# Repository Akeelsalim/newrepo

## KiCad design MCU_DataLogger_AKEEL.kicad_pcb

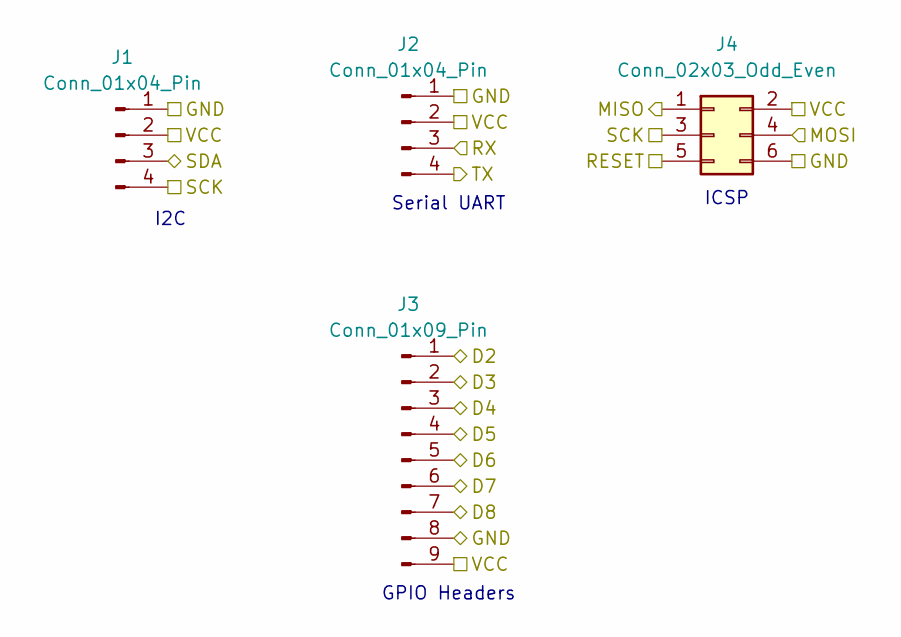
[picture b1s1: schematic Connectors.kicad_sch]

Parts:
J1, J2: Conn_01x04_Pin; PinHeader_1x04_P2.54mm_Vertical
J3: Conn_01x09_Pin; PinHeader_1x09_P2.54mm_Vertical
J4: Conn_02x03_Odd_Even; PinHeader_2x03_P2.54mm_Vertical

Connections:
/D2: J3.1; also elsewhere on the board
/D3: J3.2; also elsewhere on the board
/D4: J3.3; also elsewhere on the board
/D5: J3.4; also elsewhere on the board
/D6: J3.5; also elsewhere on the board
/D7: J3.6; also elsewhere on the board
/D8: J3.7; also elsewhere on the board
/MISO: J4.1; also elsewhere on the board
/MOSI: J4.4; also elsewhere on the board
/RESET: J4.5; also elsewhere on the board
/RX: J2.3; also elsewhere on the board
/SCK: J1.4, J4.3; also elsewhere on the board
/SDA: J1.3; also elsewhere on the board
/TX: J2.4; also elsewhere on the board
/VCC: J1.2, J2.2, J3.9, J4.2; also elsewhere on the board
GND: J1.1, J2.1, J3.8, J4.6; also elsewhere on the board

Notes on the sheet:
ICSP
Serial UART
I2C
GPIO Headers

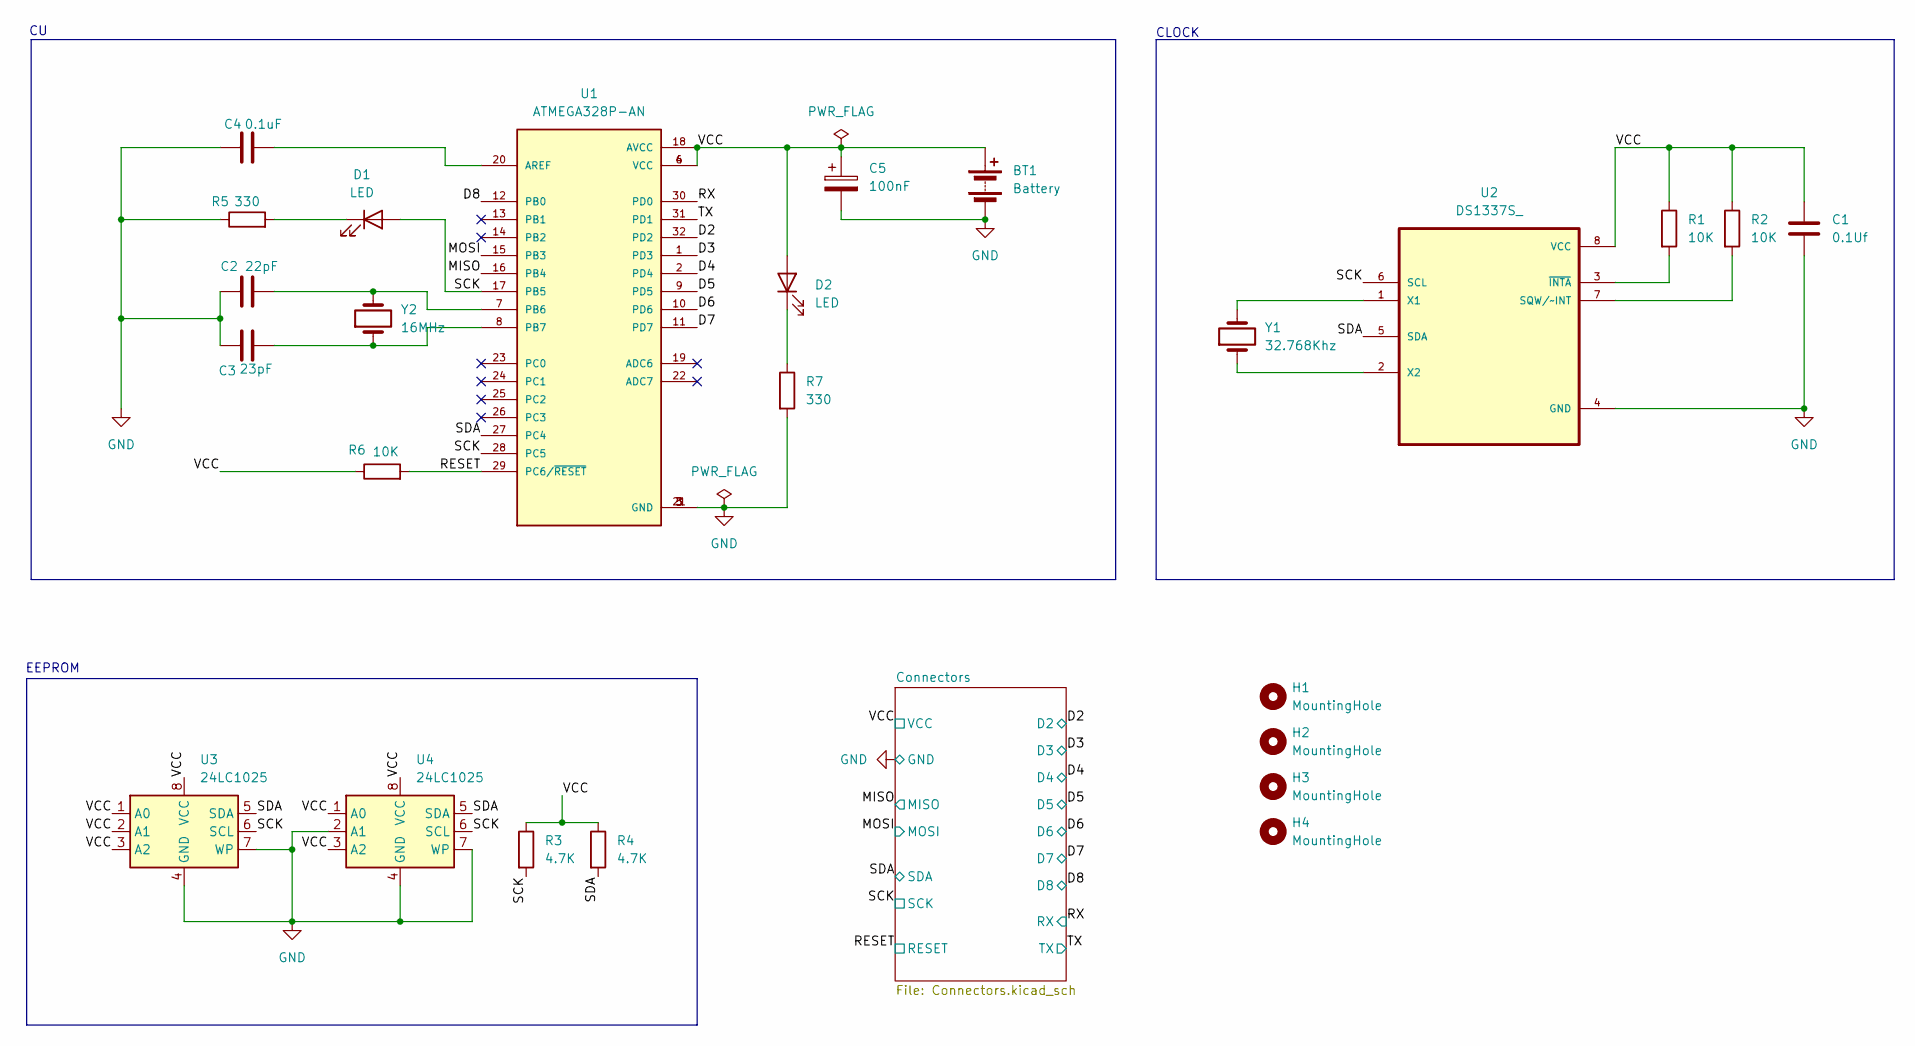
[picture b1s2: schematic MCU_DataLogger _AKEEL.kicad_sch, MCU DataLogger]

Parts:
BT1: Battery; PinHeader_1x02_P2.54mm_Vertical
C1: 0.1Uf; C_0805_2012Metric
C2: 22pF; C_0805_2012Metric
C3: 23pF; C_0805_2012Metric
C4: 0.1uF; C_0805_2012Metric
C5: 100nF; C_0805_2012Metric
D1, D2: LED; LED_0805_2012Metric
H1, H2, H3, H4: MountingHole; MountingHole_2.1mm
R1, R2, R6: 10K; R_0805_2012Metric
R3, R4: 4.7K; R_0805_2012Metric
R5, R7: 330; R_0805_2012Metric
U1: ATMEGA328P-AN; Atmega328p-AN
U2: DS1337S_; DS1337S
U3, U4: 24LC1025; SOIC-8_5.3x5.3mm_P1.27mm
Y1: 32.768Khz; Crystal_SMD_5032-2Pin_5.0x3.2mm_HandSoldering
Y2: 16MHz; Crystal_SMD_5032-2Pin_5.0x3.2mm_HandSoldering

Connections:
/D2: U1.32 (PD2); also elsewhere on the board
/D3: U1.1 (PD3); also elsewhere on the board
/D4: U1.2 (PD4); also elsewhere on the board
/D5: U1.9 (PD5); also elsewhere on the board
/D6: U1.10 (PD6); also elsewhere on the board
/D7: U1.11 (PD7); also elsewhere on the board
/D8: U1.12 (PB0); also elsewhere on the board
/MISO: U1.16 (PB4); also elsewhere on the board
/MOSI: U1.15 (PB3); also elsewhere on the board
/RESET: R6.2, U1.29 (PC6/~RESET); also elsewhere on the board
/RX: U1.30 (PD0); also elsewhere on the board
/SCK: D1.2 (A), R3.2, U1.17 (PB5), U1.28 (PC5), U2.6 (SCL), U3.6 (SCL), U4.6 (SCL); also elsewhere on the board
/SDA: R4.2, U1.27 (PC4), U2.5 (SDA), U3.5 (SDA), U4.5 (SDA); also elsewhere on the board
/TX: U1.31 (PD1); also elsewhere on the board
/VCC: BT1.1 (+), C1.1, C5.1, D2.2 (A), R1.1, R2.1, R3.1, R4.1, R6.1, U1.4 (VCC), U1.6 (VCC), U1.18 (AVCC), U2.8 (VCC), U3.1 (A0), U3.2 (A1), U3.3 (A2), U3.8 (VCC), U4.1 (A0), U4.3 (A2), U4.8 (VCC); also elsewhere on the board
GND: BT1.2 (-), C1.2, C2.1, C3.1, C4.1, C5.2, R5.1, R7.2, U1.3 (GND), U1.5 (GND), U1.21 (GND), U2.4 (GND), U3.4 (GND), U3.7 (WP), U4.2 (A1), U4.4 (GND), U4.7 (WP); also elsewhere on the board
unnamed: D1.1 (K), R5.2
unnamed: D2.1 (K), R7.1
unnamed: C4.2, U1.20 (AREF)
unnamed: C2.2, U1.7 (PB6), Y2.2
unnamed: C3.2, U1.8 (PB7), Y2.1
unnamed: R2.2, U2.7 (SQW/~INT)
unnamed: U2.1 (X1), Y1.2
unnamed: U2.2 (X2), Y1.1
unnamed: R1.2, U2.3 (~INTA)

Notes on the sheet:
EEPROM
CLOCK

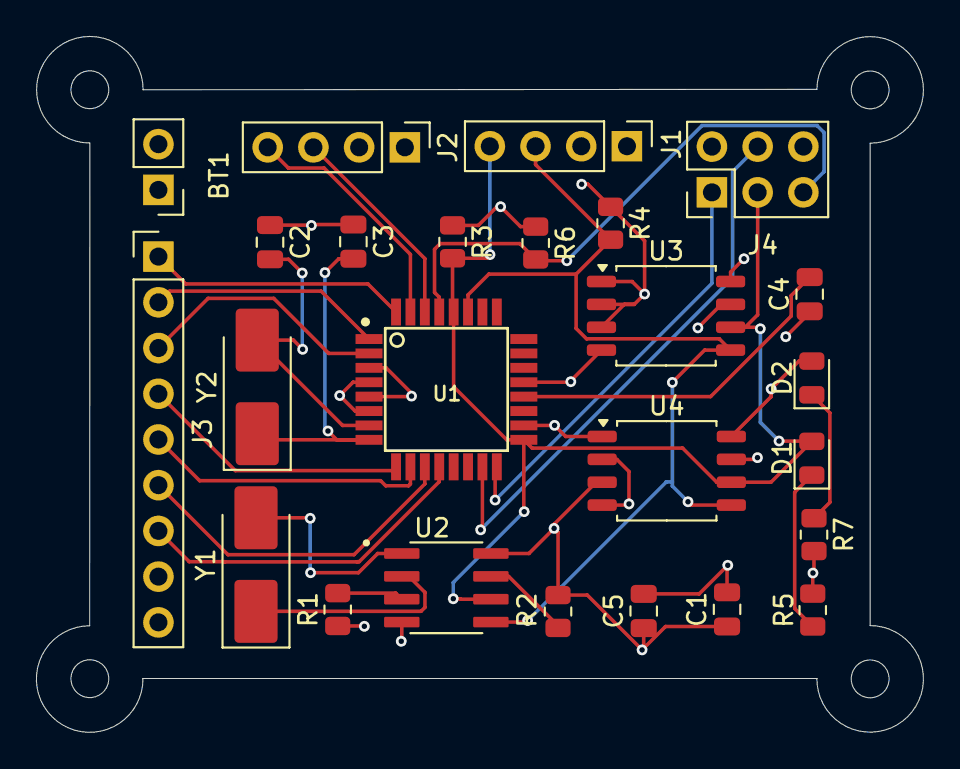
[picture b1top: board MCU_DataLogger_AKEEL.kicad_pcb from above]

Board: 4 copper layers, 49.3 x 38.7 mm, 29 parts (0 on the bottom side), 25 nets.
